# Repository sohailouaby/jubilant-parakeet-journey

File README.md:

# Jubilant-parakeet-Journey
### made by Sohail Ouabdallah

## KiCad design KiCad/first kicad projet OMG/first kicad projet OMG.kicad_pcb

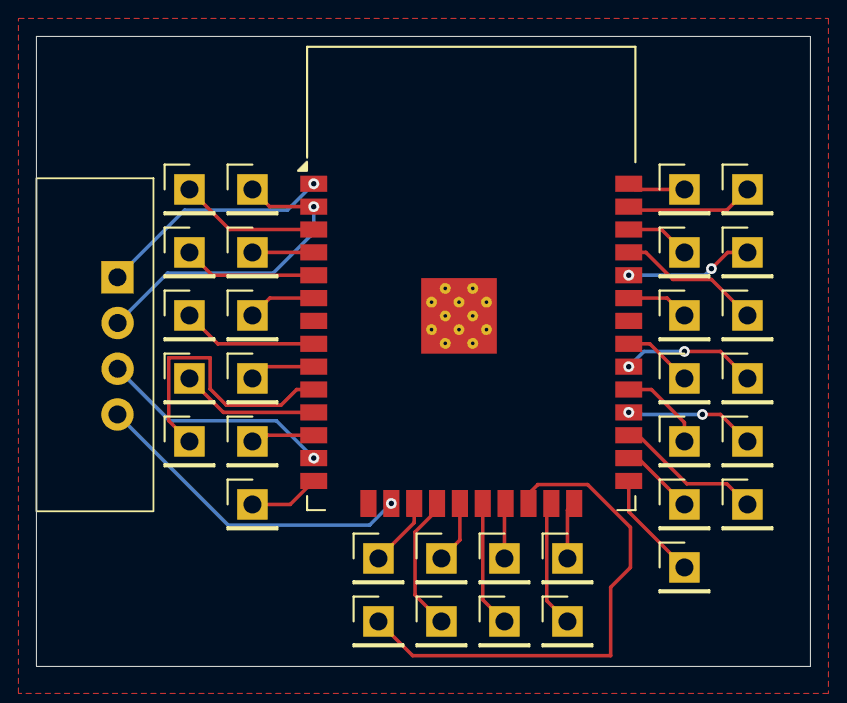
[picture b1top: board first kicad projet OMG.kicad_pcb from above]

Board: 2 copper layers, 43.0 x 35.0 mm, 34 parts (0 on the bottom side), 34 nets.

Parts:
J5, J6, J7, J8, J9, J10, J11, J12, J13, J14, J15, J16, J17, J18, J19, J20, J21, J22, J23, J24, J25, J26, J27, J28, J29, J30, J31, J32, J33, J34, J35, J36: Conn_01x01_Pin; PinHeader_1x01_P2.54mm_Vertical
U1: ESP32-WROOM-32
U2: ER_OLEDM0.91_1x-I2C; OLED display for esp32

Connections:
+3.3V: J26.1 (Pin_1_1), U1.2 (VDD), U2.2 (VCC)
GND: J27.1 (Pin_1_1), U1.1 (GND), U1.15 (GND), U1.38 (GND), U1.39 (GND), U2.1 (GND)
unnamed: J5.1 (Pin_1_1), U1.6 (IO34)
unnamed: J6.1 (Pin_1_1), U1.9 (IO33)
unnamed: J7.1 (Pin_1_1), U1.8 (IO32)
unnamed: J8.1 (Pin_1_1), U1.12 (IO27)
unnamed: J9.1 (Pin_1_1), U1.11 (IO26)
unnamed: J10.1 (Pin_1_1), U1.10 (IO25)
unnamed: J11.1 (Pin_1_1), U1.37 (IO23)
unnamed: J12.1 (Pin_1_1), U1.36 (IO22)
unnamed: J13.1 (Pin_1_1), U1.33 (IO21)
unnamed: J14.1 (Pin_1_1), U1.31 (IO19)
unnamed: J15.1 (Pin_1_1), U1.30 (IO18)
unnamed: J16.1 (Pin_1_1), U1.28 (IO17)
unnamed: J17.1 (Pin_1_1), U1.27 (IO16)
unnamed: J18.1 (Pin_1_1), U1.23 (IO15)
unnamed: J19.1 (Pin_1_1), U1.14 (IO12)
unnamed: J20.1 (Pin_1_1), U1.29 (IO5)
unnamed: J21.1 (Pin_1_1), U1.26 (IO4)
unnamed: J22.1 (Pin_1_1), U1.34 (RXD0/IO3)
unnamed: J23.1 (Pin_1_1), U1.24 (IO2)
unnamed: J24.1 (Pin_1_1), U1.35 (TXD0/IO1)
unnamed: J25.1 (Pin_1_1), U1.25 (IO0)
unnamed: J28.1 (Pin_1_1), U1.19 (SCS/CMD)
unnamed: J29.1 (Pin_1_1), U1.20 (SCK/CLK)
unnamed: J30.1 (Pin_1_1), U1.18 (SWP/SD3)
unnamed: J31.1 (Pin_1_1), U1.17 (SHD/SD2)
unnamed: J32.1 (Pin_1_1), U1.22 (SDI/SD1)
unnamed: J33.1 (Pin_1_1), U1.21 (SDO/SD0)
unnamed: J34.1 (Pin_1_1), U1.5 (SENSOR_VN)
unnamed: J35.1 (Pin_1_1), U1.4 (SENSOR_VP)
unnamed: J36.1 (Pin_1_1), U1.3 (EN)
unnamed: U1.16 (IO13), U2.3 (SCL)
unnamed: U1.13 (IO14), U2.4 (SDA)
